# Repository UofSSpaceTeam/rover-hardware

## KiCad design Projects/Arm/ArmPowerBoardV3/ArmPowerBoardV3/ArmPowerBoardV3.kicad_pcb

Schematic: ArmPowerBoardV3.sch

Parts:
BT1: 24vin; TerminalBlock_1x02_P5.08mm_Horizontal
C1, C7, C9, C10, C11: 100nF; C_0805_2012Metric_Pad1.15x1.40mm_HandSolder
C2, C4: 22pF; C_0805_2012Metric_Pad1.15x1.40mm_HandSolder
C3: 220uF; CP_Elec_8x10
C5, C6: 10pF; C_0805_2012Metric_Pad1.15x1.40mm_HandSolder
C8: 10 uF; C_0805_2012Metric_Pad1.15x1.40mm_HandSolder
D1: D_Zener; D_SMB_Handsoldering
D2: LED; LED_D5.0mm_IRGrey
J1: Screw_Terminal_01x04; TerminalBlock_Big4pin
J2, J3, J5, J6, J7: Barrel_Jack; BarrelJack_Wuerth_6941xx301002
J4: Screw_Terminal_01x02; TerminalBlock_1x02_P5.08mm_Horizontal
J8: Gpio out; PinHeader_2x10_P2.54mm_Vertical
J9: Breakout L; PinHeader_1x09_P2.54mm_Vertical
J10: Atmega Holder; DIP-28_W7.62mm
J11: Breakout R; PinHeader_1x09_P2.54mm_Vertical
J13: JST serial; JST_PH_B7B-PH-SM4-TB_1x07-1MP_P2.00mm_Vertical
R2: R; R_Axial_DIN0204_L3.6mm_D1.6mm_P5.08mm_Horizontal
U1: ACS758; Allegro_CB_PSF
U2: VHB200W-Q24-S12; CONV_VHB200W-Q24-S12
U3: V7805-1000
U4: Temp sense; SOT-23_Handsoldering
Y1: Crystal; Crystal_HC49-U_Vertical

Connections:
5v+: C1.2, C6.1, C7.2, C9.2, C10.2, C11.2, J5.1, J6.1, J7.1, J8.1, J8.2, J8.3, J8.4, J9.4, J10.7, J10.20, J10.21, J13.7, U1.1, U3.3 (OUT), U4.1
12v+: J1.2, J1.4, J2.1, J3.1, U2.9
12v-: J1.1, J1.3, J2.2, J3.2, U2.5
24v: C5.1, J4.2, U1.5, U2.1, U3.1 (IN)
GND: BT1.1, C1.1, C2.2, C3.2, C4.2, C5.2, C6.2, C7.1, C8.2, C9.1, C10.1, C11.1, D1.2, J4.1, J5.2, J6.2, J7.2, J8.18, J8.19, J8.20, J9.1, J10.8, J10.22, J13.5, R2.2, U1.2, U2.4, U3.2 (GND), U4.3
ISense: J10.23, U1.3
unnamed: BT1.2, C3.1, C8.1, D1.1, U1.4
unnamed: C2.1, J10.9, Y1.1
unnamed: C4.1, J10.10, Y1.2
unnamed: D2.1, R2.1
unnamed: D2.2, J10.4
unnamed: J8.10, J10.1
unnamed: J8.9, J10.5
unnamed: J8.8, J10.11
unnamed: J8.7, J10.12
unnamed: J8.6, J10.13
unnamed: J8.5, J10.14
unnamed: J8.17, J10.17
unnamed: J8.16, J10.18
unnamed: J8.15, J10.19
unnamed: J8.14, J10.25
unnamed: J8.13, J10.26
unnamed: J8.12, J10.27
unnamed: J8.11, J10.28
ONoff: J10.6, U2.2
RX1: J10.15, J13.2
Rx: J10.2, J11.9
TX1: J10.16, J13.3
TempSense: J10.24, U4.2
Tx: J10.3, J11.5

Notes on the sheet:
Power IN
Temperature Sensor
Headers for USB breakoutboard
JST UART Port
12v Power Supply
Power OUT
5v Power Supply
MCU
change to 0805

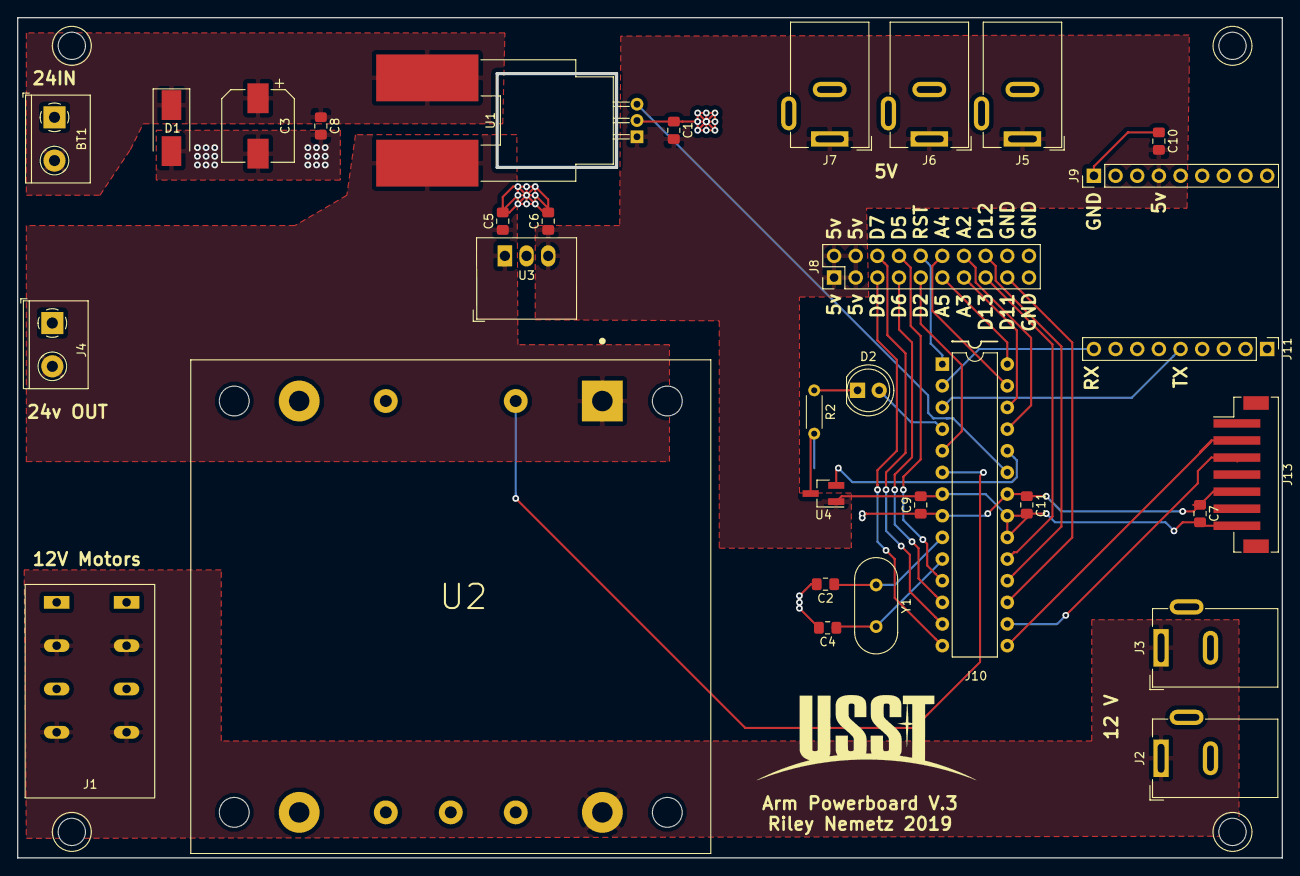
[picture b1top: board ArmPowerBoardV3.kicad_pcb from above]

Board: 2 copper layers, 148.3 x 98.6 mm, 32 parts (0 on the bottom side), 30 nets.

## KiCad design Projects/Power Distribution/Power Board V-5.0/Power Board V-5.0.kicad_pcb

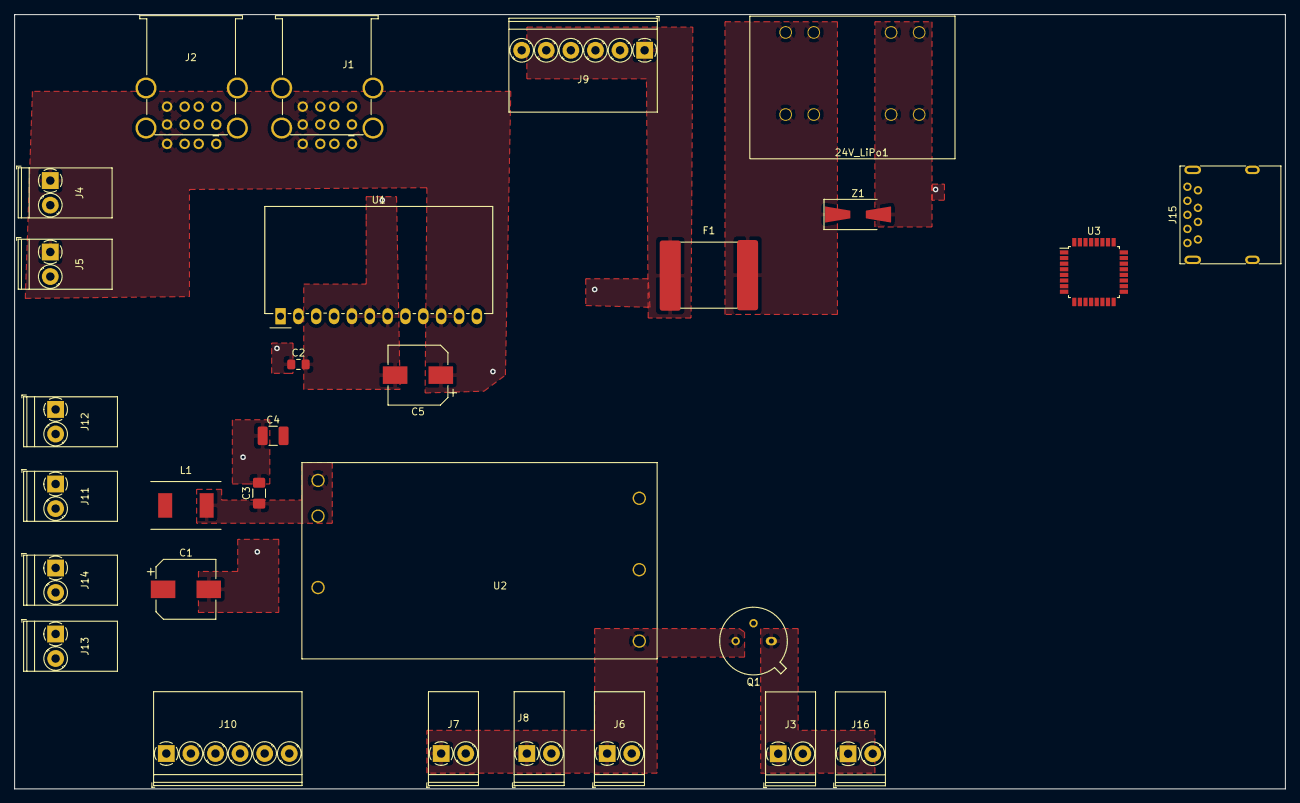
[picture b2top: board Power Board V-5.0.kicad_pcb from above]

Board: 2 copper layers, 180.8 x 110.2 mm, 29 parts (0 on the bottom side), 11 nets, no tracks yet.

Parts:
24V_LiPo1: Battery; Molex_80A
C1, C5: 100uF; CP_Elec_8x10
C2: 1uF; C_0805_2012Metric_Pad1.15x1.40mm_HandSolder
C3: 6.8uF; C_1206_3216Metric_Pad1.42x1.75mm_HandSolder
C4: 6.8nF; C_1210_3225Metric_Pad1.42x2.65mm_HandSolder
F1: 80A; 80A_SMD_Fuse
J1: Pi+Jet; USB_A_PowerONLY_3Stacked
J2: USB xtra; USB_A_PowerONLY_3Stacked
J3, J16: Fans; 2Pos_Tilt_Pheonix
J4, J5: 5v xtra; 2Pos_Tilt_Pheonix
J6: ETH; 2Pos_Tilt_Pheonix
J7, J8: 12v xtra; 2Pos_Tilt_Pheonix
J9: Motors Right terminal; 6Pos_Tilt_Pheonix
J10: Motors left terminal; 6Pos_Tilt_Pheonix
J11: Arm 24v; 2Pos_Tilt_Pheonix
J12: Fr. Atch 24v; 2Pos_Tilt_Pheonix
J13, J14: 24v xtra; 2Pos_Tilt_Pheonix
J15: USB3_A; USB3_A_Molex_48393-001
L1: 4.7uH; Inductor_4.7uH
Q1: 2N2219; TO-39-3
U1: R-745; Converter_DCDC_RECOM_R5xxxDA_THT
U2: RPA60-2412SFW; RPA60
U3: STM8S003K3T; LQFP-32_7x7mm_P0.8mm
Z1: 3w; D_SMA-SMB_Universal_Handsoldering

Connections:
5v+: C5.1, J1.1, J2.1, J4.1, J5.1, U1.9, U1.10, U1.11, U3.7
12v+: J6.1, J7.1, J8.1, Q1.3, U2.6
12v-: C4.2, J3.2, J6.2, J7.2, J8.2, J16.2, U2.5
24v: C1.1, C2.1, F1.1, J9.1, J9.3, J9.5, J10.1, J10.3, J10.5, J11.1, J12.1, J13.1, J14.1, L1.1, U1.2, U1.3, U1.4
GND: 24V_LiPo1.2, C1.2, C2.2, C3.2, C4.1, C5.2, J1.4, J2.4, J4.2, J5.2, J9.2, J9.4, J9.6, J10.2, J10.4, J10.6, J11.2, J12.2, J13.2, J14.2, U1.5, U1.6, U1.7, U1.8, U2.2, U3.4, Z1.2
unnamed: 24V_LiPo1.1, F1.2, Z1.1
unnamed: C3.1, L1.2, U2.1
unnamed: J3.1, J16.1, Q1.1
SCL1_B: J15.8, U3.24
SDA0_B: J15.2, U3.8
SDA1_B: J15.3, U3.23

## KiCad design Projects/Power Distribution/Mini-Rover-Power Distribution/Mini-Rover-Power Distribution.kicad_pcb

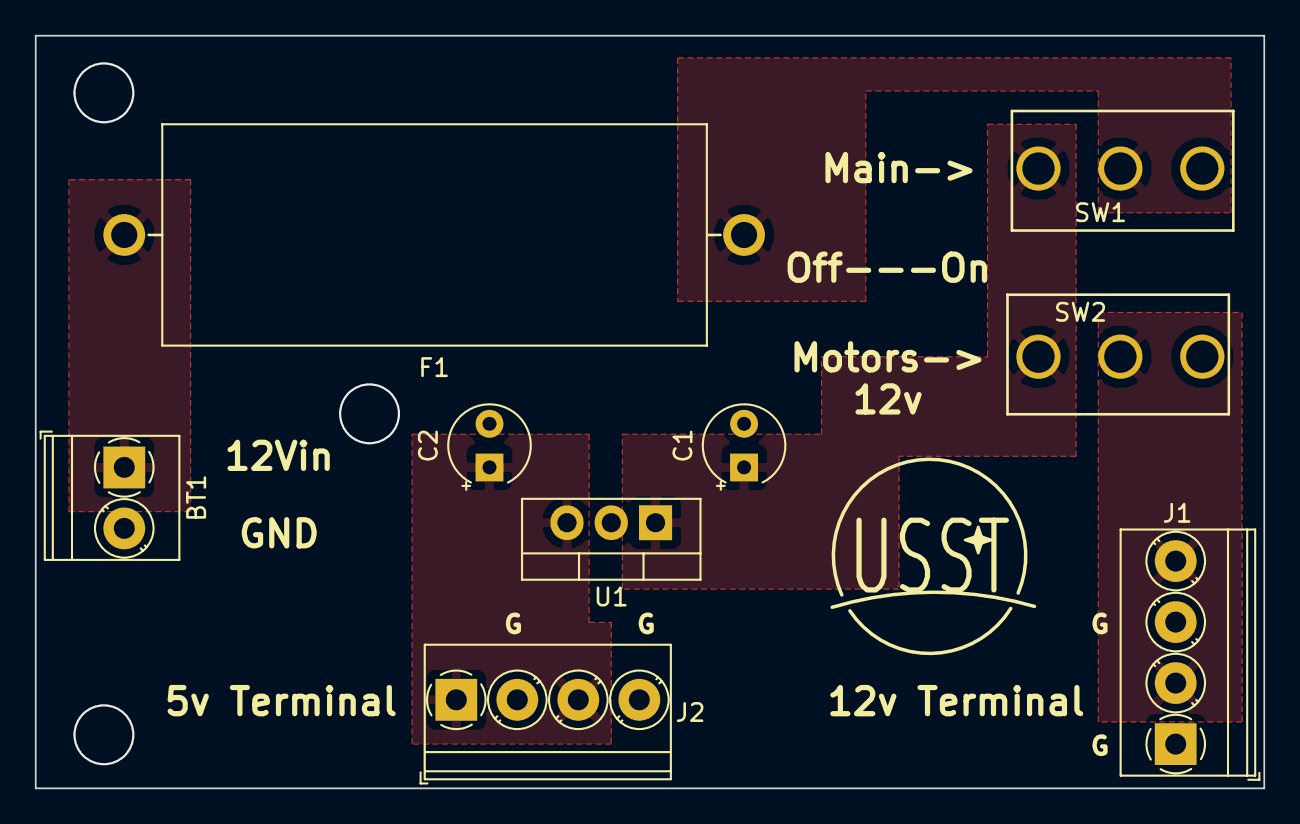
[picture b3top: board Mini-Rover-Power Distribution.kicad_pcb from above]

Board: 2 copper layers, 70.5 x 43.2 mm, 9 parts (0 on the bottom side), 6 nets, no tracks yet.

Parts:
BT1: Battery; TerminalBlock_Phoenix_PT-1,5-2-3.5-H_1x02_P3.50mm_Horizontal
C1: u 0.22F; CP_Radial_Tantal_D4.5mm_P2.50mm
C2: u 0.1F; CP_Radial_Tantal_D4.5mm_P2.50mm
F1: 6.3 A; LittleFuseHolder-03540101ZXGY-
J1, J2: Screw_Terminal_01x04; TerminalBlock_Phoenix_PT-1,5-4-3.5-H_1x04_P3.50mm_Horizontal
SW1, SW2: Toggle Switch; Switch_Toggle
U1: LM7805CT/NOPB; TO-220-3_Vertical

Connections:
/5v: C2.1, J2.1, J2.3, U1.3
/12v: BT1.1, F1.1
GND: BT1.2, C1.2, C2.2, J1.1, J1.3, J2.2, J2.4, U1.2
unnamed: C1.1, SW1.1, SW2.3, U1.1
unnamed: F1.2, SW1.2
unnamed: J1.2, J1.4, SW2.2

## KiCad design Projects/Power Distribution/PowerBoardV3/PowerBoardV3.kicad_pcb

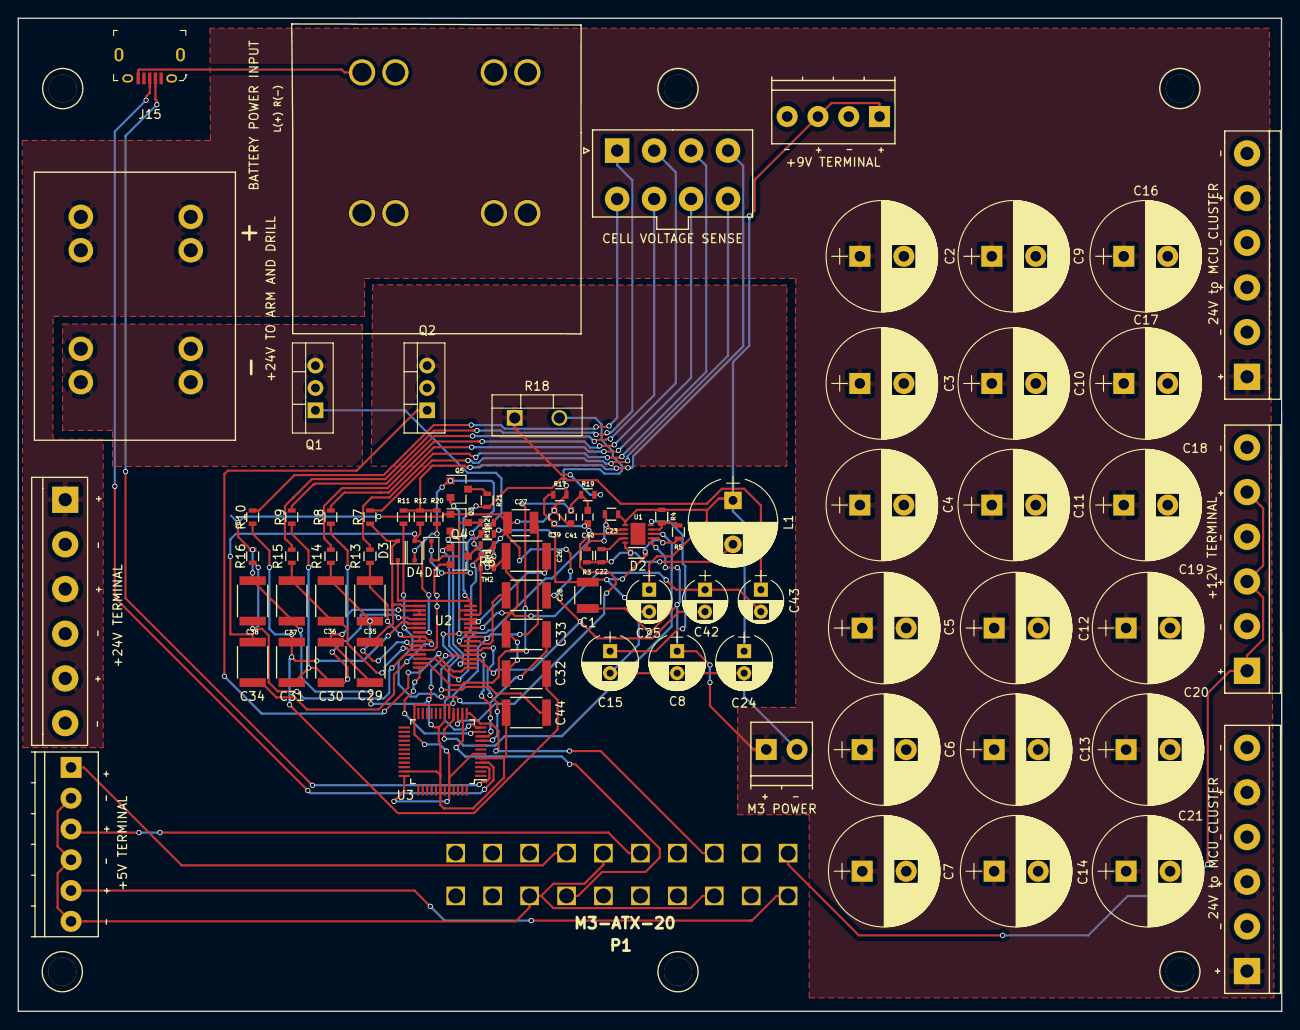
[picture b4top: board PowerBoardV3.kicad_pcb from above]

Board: 2 copper layers, 143.7 x 112.9 mm, 92 parts (0 on the bottom side), 60 nets.

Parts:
24V to MCU CLUSTER: MC_STACK_2; TerminalBlock_Pheonix_PT-5mm_6pol
24V to MCU CLUSTER#2: MC_STACK_1; TerminalBlock_Pheonix_PT-5mm_6pol
+5V TERMINAL: 5V_INT_PWR_BLK; TerminalBlock_Phoenix_PT-3.5mm_6pol
+9V TERMINAL: 9V_PWR_TERMBLK; TerminalBlock_Pheonix_PT-3.5mm_4pol
+12V TERMINAL: 12V_INT_PWR_BLK; TerminalBlock_Pheonix_PT-5mm_6pol
+24V TERMINAL: 24V_INT_PWR_BLK; TerminalBlock_Pheonix_PT-5mm_6pol
+24V TO ARM AND DRILL: BACK_EXT_24V; Phoenix_Contact_1770539
BATTERY POWER INPUT: BATT_PWR; Phoenix_Contact_1845344_Ver2
C1: 4.7uF; C_1210
C2, C3, C4, C5, C6, C7, C9, C10, C11, C12, C13, C14, C16, C17, C18, C19, C20, C21: 680uF; CP_Radial_D12.5mm_P5.00mm
C8, C15: 100uF; CP_Radial_D6.3mm_P2.50mm
C22, C23: 10nF; R_0603
C24: 68uF; CP_Radial_D6.3mm_P2.50mm
C25: 10uF; CP_Radial_D5.0mm_P2.50mm
C26, C28, C29, C30, C31, C32, C33, C34, C35, C36, C37, C38, C44: 1 uF; C_1812
C27: 4.7 uF; C_1210
C39, C40, C41: 0.1uF; C_0603
C42, C43: 10 uF; CP_Radial_D5.0mm_P2.50mm
CELL VOLTAGE SENSE: Cell Voltage Sense; Molex_MiniFit-JR-5556-08A_2x04x4.20mm_Straight
D1: D_Small_ALT; D_SOD-323F
D2: D_Zener_Small_ALT; D_0603
D3, D4: D_Small; D_SOD-323F
J15: USB_OTG; USB_Micro_B_Female_10118194-0001LF
L1: 39uH; CP_Radial_D10.0mm_P5.00mm
M3 POWER: M3-ATX-20-PWR; TerminalBlock_Phoenix_PT-3.5mm_2pol
P1: M3-ATX-20; ATX20
Q1, Q2: IRF3205; TO-220-3_Vertical
Q3: BSS84; SOT-23
Q4: BSS83P; SOT-23
Q5: BSS138; SOT-23
R1, R2: 1M; R_0603
R3: 20k; R_0603
R4: 300k; R_0603
R5: 30k; R_0603
R6: 10k; R_0603
R7, R8, R9, R10, R11, R12, R13, R14, R15, R16: 1k; R_0603
R17, R19, R20, R21: 100; R_0603
R18: 5m; TO-220-2_Vertical_Ver2
TH1, TH2: 10k; R_0603
U1: MP2492; QFN_10
U2: bq76930; 30-TSSOP
U3: SAMD21; TQFP-48_7x7mm_Pitch0.5mm

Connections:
+5V_1: +5V TERMINAL.1, P1.7
+5V_2: +5V TERMINAL.3, P1.11
+5V_3: +5V TERMINAL.5, P1.20
+9V: +9V TERMINAL.1, +9V TERMINAL.3, C23.1, C24.1, C25.1, L1.1, R4.1, U1.6
+12V: +12V TERMINAL.1, +12V TERMINAL.3, +12V TERMINAL.5, P1.19
-5V: +5V TERMINAL.2, +5V TERMINAL.4, +5V TERMINAL.6, P1.6, P1.9, P1.16
-12V: 24V to MCU CLUSTER.2, 24V to MCU CLUSTER.4, 24V to MCU CLUSTER.6, 24V to MCU CLUSTER#2.2, 24V to MCU CLUSTER#2.4, 24V to MCU CLUSTER#2.6, +9V TERMINAL.2, +9V TERMINAL.4, +12V TERMINAL.2, +12V TERMINAL.4, +12V TERMINAL.6, +24V TERMINAL.2, +24V TERMINAL.4, +24V TERMINAL.6, +24V TO ARM AND DRILL.2, C1.2, C2.2, C3.2, C4.2, C5.2, C6.2, C7.2, C8.2, C9.2, C10.2, C11.2, C12.2, C13.2, C14.2, C15.2, C16.2, C17.2, C18.2, C19.2, C20.2, C21.2, C24.2, C25.2, D2.2, M3 POWER.2, P1.10, P1.12, P1.14, Q1.3, R1.2, R5.2, U1.2
/HighPowerCircuit/9V_EN: U1.3, U3.16
/HighPowerCircuit/CHG: Q3.2, U2.2
/HighPowerCircuit/CHG_T: Q1.2, Q2.2
/HighPowerCircuit/DSG: Q2.1, U2.1
/HighPowerCircuit/FB: R4.2, R5.1, U1.4
/HighPowerCircuit/PG: P1.15, U3.13
/HighPowerCircuit/SENSE_R: Q2.3, R18.1, R19.1
/Low Power Circuit /9V_PGOOD: U1.8, U3.15
/Low Power Circuit /PG: P1.8, U3.14
A: CELL VOLTAGE SENSE.4, R11.1, R12.1, R20.2
ALERT: U2.30, U3.11
BAT1: C43.1, D3.1, R21.2, U2.15
BATT+: 24V to MCU CLUSTER.1, 24V to MCU CLUSTER.3, 24V to MCU CLUSTER.5, 24V to MCU CLUSTER#2.1, 24V to MCU CLUSTER#2.3, 24V to MCU CLUSTER#2.5, +24V TERMINAL.1, +24V TERMINAL.3, +24V TERMINAL.5, +24V TO ARM AND DRILL.1, BATTERY POWER INPUT.2, C1.1, C2.1, C3.1, C4.1, C5.1, C6.1, C7.1, C8.1, C9.1, C10.1, C11.1, C12.1, C13.1, C14.1, C16.1, C17.1, C18.1, C19.1, C20.1, C21.1, M3 POWER.1, U1.1
BOOT_MC: Q4.1, U3.12
BOOT_TS1: Q4.3, R6.2
BOOT_VC1: C36.1, C37.2, Q4.2, R15.2, U2.26
CAP2: C26.1, C32.1, C33.2, C42.1, C43.2, D4.1, Q5.1, R20.1, TH2.2, U2.10
CELL_1+: CELL VOLTAGE SENSE.1, R15.1
CELL_2+: CELL VOLTAGE SENSE.2, R14.1
CELL_3+: CELL VOLTAGE SENSE.3, R13.1
CELL_5+: CELL VOLTAGE SENSE.5, R10.1
CELL_6+: CELL VOLTAGE SENSE.6, R9.1
CELL_7+: CELL VOLTAGE SENSE.7, R8.1
CELL_8+: CELL VOLTAGE SENSE.8, R7.1
Cell_1-: BATTERY POWER INPUT.1, C27.2, C28.1, C37.1, C38.2, C39.1, C41.2, C42.2, C44.2, J15.5, Q3.1, R16.1, R17.1, R18.2, TH1.2, U2.3, U3.5, U3.18, U3.35, U3.42
unnamed: C15.1, U1.5
unnamed: C22.1, D2.1, L1.2, R3.2, U1.10
unnamed: C22.2, U1.9
unnamed: C23.2, R3.1, U1.7
unnamed: C26.2, U2.11, U2.12, U2.14
unnamed: C28.2, U2.7
unnamed: C29.1, C30.2, R8.2, U2.17, U2.18
unnamed: C29.2, D3.2, R7.2, U2.16
unnamed: C30.1, C31.2, R9.2, U2.19
unnamed: C31.1, C32.2, R10.2, U2.20
unnamed: C33.1, R11.2, U2.21
unnamed: C34.1, C35.2, R13.2, U2.23, U2.24
unnamed: C34.2, D4.2, R12.2, U2.22
unnamed: C35.1, C36.2, R14.2, U2.25
unnamed: C38.1, R16.2, U2.27
unnamed: D1.1, Q1.1, R1.1, R2.2
unnamed: D1.2, Q3.3, R2.1
unnamed: Q5.3, R21.1
unnamed: R6.1, TH1.1, U2.6
unnamed: TH2.1, U2.13
REGSRC: C44.1, Q5.2, U2.9
SCL: U2.5, U3.9
SDA: U2.4, U3.10
SRN: C40.2, C41.1, R19.2, U2.29
SRP: C39.2, C40.1, R17.2, U2.28
USB_D+: J15.3, U3.4
USB_D-: J15.2, U3.3
VCC: C27.1, U2.8, U3.6, U3.17, U3.36, U3.44

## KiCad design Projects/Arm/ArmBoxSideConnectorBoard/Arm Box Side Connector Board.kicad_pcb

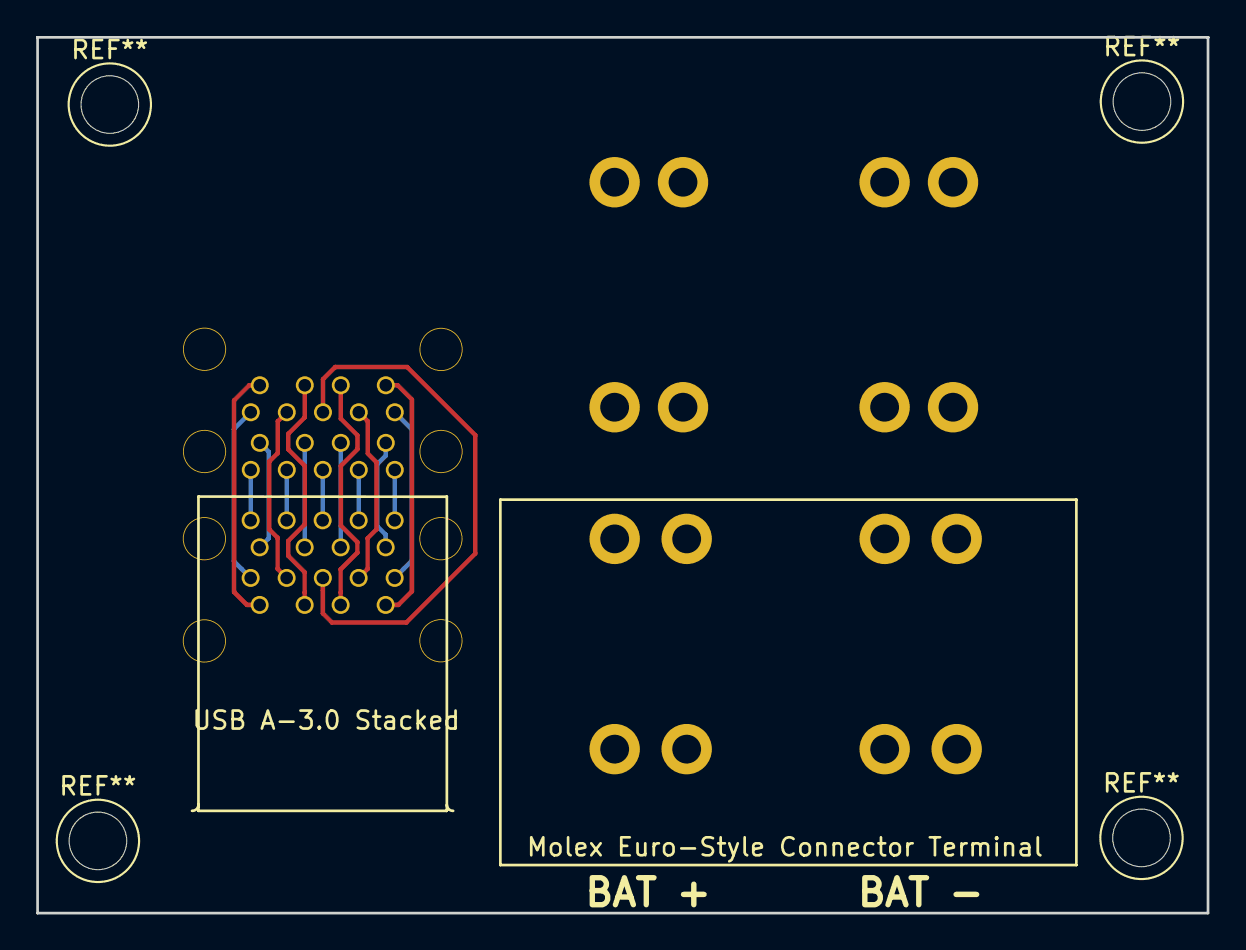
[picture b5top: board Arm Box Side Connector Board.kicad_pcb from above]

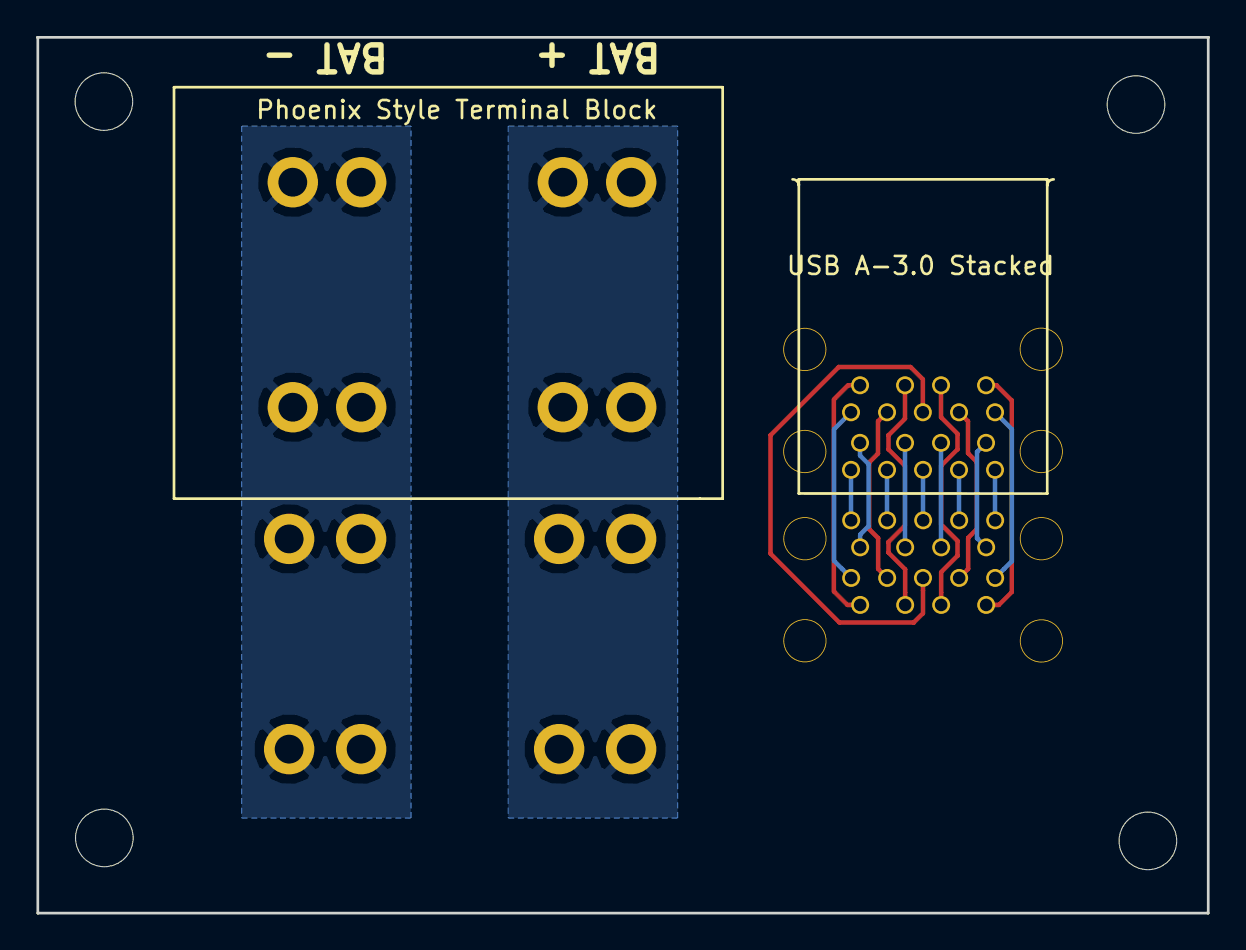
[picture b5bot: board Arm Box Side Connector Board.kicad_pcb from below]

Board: 2 copper layers, 65.1 x 48.7 mm, 4 parts (2 on the bottom side), 20 nets.

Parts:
Molex Euro-Style Connector Terminal: PowerConnector; MolexEuroStyleTerminalBlock2Position
Phoenix Style Terminal Block: PowerConnector; Phoenix_Contact_1770539
USB A-3.0 Stacked, USB A-3.0 Stacked#2: Conn_02x09_Odd_Even; USB-A_3.0_Stacked_WM10420-ND

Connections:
unnamed: USB A-3.0 Stacked.1, USB A-3.0 Stacked#2.1
unnamed: USB A-3.0 Stacked.2, USB A-3.0 Stacked#2.2
unnamed: USB A-3.0 Stacked.3, USB A-3.0 Stacked#2.3
unnamed: USB A-3.0 Stacked.4, USB A-3.0 Stacked#2.4
unnamed: USB A-3.0 Stacked.5, USB A-3.0 Stacked#2.5
unnamed: USB A-3.0 Stacked.6, USB A-3.0 Stacked#2.6
unnamed: USB A-3.0 Stacked.7, USB A-3.0 Stacked#2.7
unnamed: USB A-3.0 Stacked.8, USB A-3.0 Stacked#2.8
unnamed: USB A-3.0 Stacked.9, USB A-3.0 Stacked#2.9
unnamed: USB A-3.0 Stacked.10, USB A-3.0 Stacked#2.10
unnamed: USB A-3.0 Stacked.11, USB A-3.0 Stacked#2.11
unnamed: USB A-3.0 Stacked.12, USB A-3.0 Stacked#2.12
unnamed: USB A-3.0 Stacked.13, USB A-3.0 Stacked#2.13
unnamed: USB A-3.0 Stacked.14, USB A-3.0 Stacked#2.14
unnamed: USB A-3.0 Stacked.15, USB A-3.0 Stacked#2.15
unnamed: USB A-3.0 Stacked.16, USB A-3.0 Stacked#2.16
unnamed: USB A-3.0 Stacked.17, USB A-3.0 Stacked#2.17
unnamed: USB A-3.0 Stacked.18, USB A-3.0 Stacked#2.18
unnamed: Molex Euro-Style Connector Terminal.1, Phoenix Style Terminal Block.1
unnamed: Molex Euro-Style Connector Terminal.2, Phoenix Style Terminal Block.2

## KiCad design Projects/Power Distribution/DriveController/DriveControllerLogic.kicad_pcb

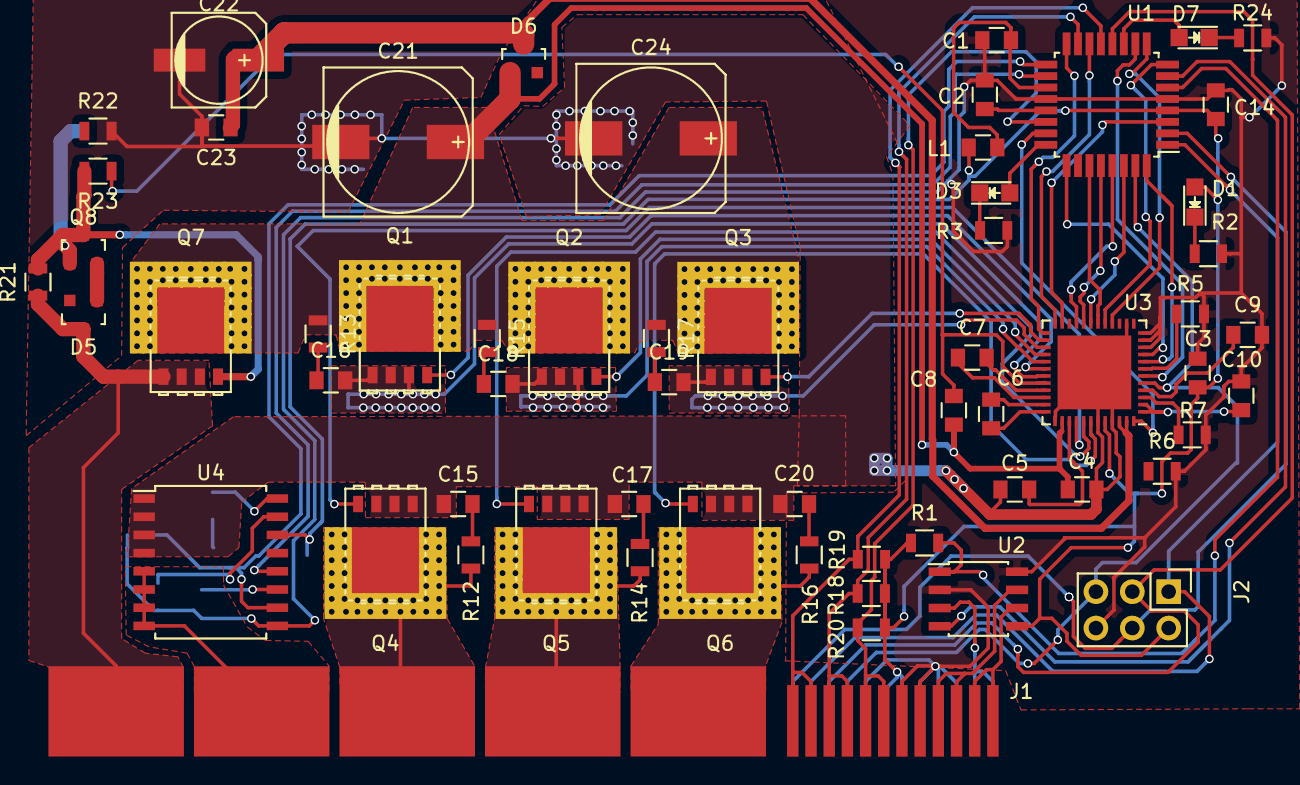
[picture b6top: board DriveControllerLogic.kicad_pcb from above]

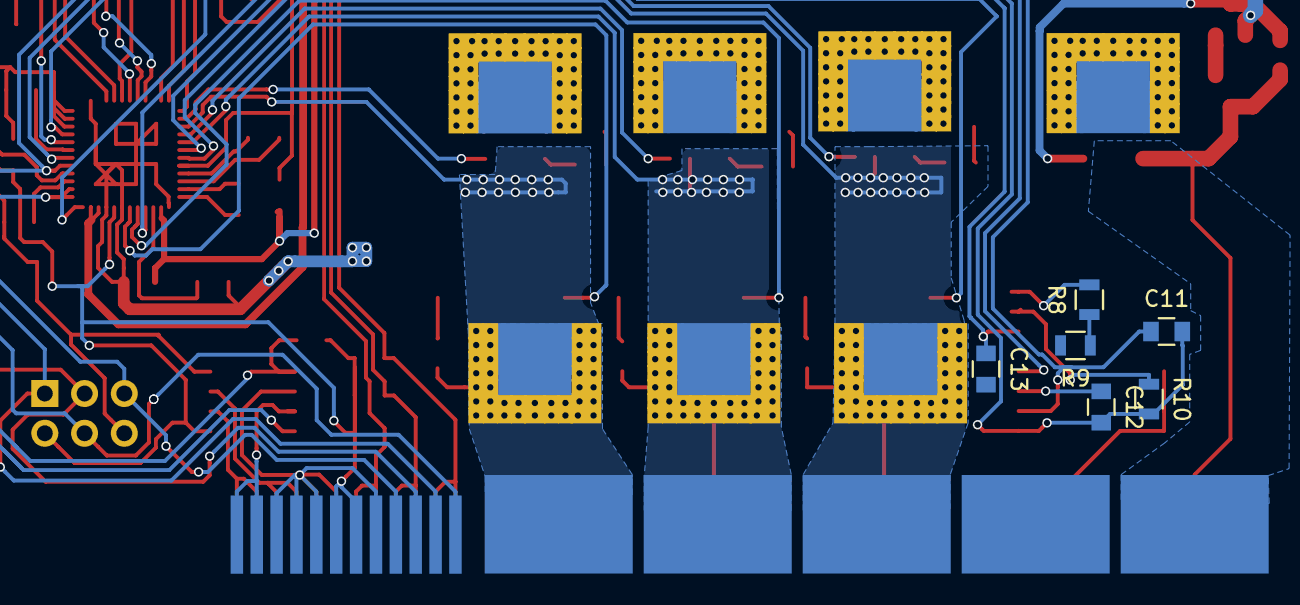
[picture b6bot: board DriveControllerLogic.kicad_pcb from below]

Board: 2 copper layers, 66 parts (6 on the bottom side), 73 nets.

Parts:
C1, C4, C6, C7, C13, C23: 100nF; C_0805
C2, C14, C15, C16, C17, C18, C19, C20: 10nF; C_0805
C3: 2.2uF; C_0805
C5, C8: 470nF; C_0805
C9: 220pF; C_0805
C10: 220nF; C_0805
C11, C12: 1nF; C_0805
C21, C24: 220uF; c_elec_10x10
C22: 22uF; c_elec_6.3x5.7
D1: LED_PWR; LED-0805
D3: LED_STAT; LED-0805
D5, D6: BAS16; SOT-23
D7: LED_CAN; LED-0805
J1: HPCE_40-24; HPCE-40-24
J2: ISP_Header; Pin_Header_Straight_2x03
L1: 10uH; C_0805
Q1, Q2, Q3, Q4, Q5, Q6, Q7: PSMN1R0; SOT-669_LFPAK_POWERSO8
Q8: BC817-40; SOT-23
R1, R6, R18, R19, R20, R22, R23: 10k; R_0805
R2, R3, R24: 1k; R_0805
R5: 0 (J); R_0805
R7: 33k; R_0805
R8, R9, R21: 100k; R_0805
R10: 47k; R_0805
R12, R13, R14, R15, R16, R17: 10; R_0805
U1: ATMega32M1; TQFP-32_7x7mm_Pitch0.8mm
U2: MCP2562; SOIC-8_3.9x4.9mm_Pitch1.27mm
U3: ATA6844; QFN-48-1EP_7x7mm_Pitch0.5mm
U4: ACS710; SOIC-16_7.5x10.3mm_Pitch1.27mm

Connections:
/5V0: C3.1, C13.1, C14.1, D1.2, J1.58, J1.59, J2.2, L1.1, R1.1, R18.1, R19.1, R20.1, U1.4, U2.5, U3.44, U4.14
/CANH: J1.49, J1.50, U2.7
/CANL: J1.51, J1.52, U2.6
/DG1: U1.3, U3.23
/DG2: U1.14, U3.24
/DG3: U1.16, U3.25
/DriveControllerPower/CPOUT: C8.2, R23.1, U3.32
/DriveControllerPower/H1: Q1.1, U3.30
/DriveControllerPower/H2: Q2.1, U3.28
/DriveControllerPower/H3: Q3.1, U3.26
/DriveControllerPower/L1: Q4.1, U3.40
/DriveControllerPower/L2: Q5.1, U3.41
/DriveControllerPower/L3: Q6.1, U3.42
/DriveControllerPower/PBAT: C4.2, C8.1, C21.1, C24.1, D6.1, Q1.5, Q2.5, Q3.5, Q7.5, R13.1, R15.1, R17.1, U3.38
/DriveControllerPower/POUT: C4.1, C5.1, C15.2, C17.2, C20.2, C21.2, C22.2, C23.2, C24.2, Q4.3, Q5.3, Q6.3, R22.2, U3.14, U3.37, U3.43, U3.45, U3.49, U4.1, U4.2, U4.3, U4.4
/DriveControllerPower/U: C16.2, J1.9, J1.29, Q1.3, Q4.5, R12.1, U3.31
/DriveControllerPower/V: C18.2, J1.13, J1.25, Q2.3, Q5.5, R14.1, U3.29
/DriveControllerPower/VBAT: C22.1, C23.1, D6.3, U3.46, U3.47
/DriveControllerPower/VSUPPLY: D5.3, J1.1, J1.37, Q7.3, R21.1
/DriveControllerPower/W: C19.2, J1.17, J1.21, Q3.3, Q6.5, R16.1, U3.27
/HA1: J1.41, J1.42, R19.2, U1.13
/HA2: J1.43, J1.44, R18.2, U1.15
/HA3: J1.45, J1.46, R20.2, U1.22
/IFL_EN: R8.2, U4.16
/IH1: U1.29, U3.21
/IH2: U1.30, U3.19
/IH3: U1.8, U3.17
/IL1: U1.28, U3.20
/IL2: U1.27, U3.18
/IL3: U1.9, U3.16
/ISENSEN: C11.1, U1.17, U4.10
/ISENSEP: U1.18, U4.12
/LGND: C1.2, C2.2, C3.2, C9.2, C10.2, C11.2, C12.2, C13.2, C14.2, J1.47, J1.48, J1.55, J1.56, J1.57, J1.60, J2.6, R2.2, R3.2, R5.2, R6.2, R7.2, R10.2, R24.2, U1.5, U1.20, U2.2, U2.8, U3.10, U3.11, U3.12, U4.9
/MISO: J1.63, J2.1, U1.1
/MOSI: J1.64, J2.4, U1.2
/NCOAST: U1.23, U3.48
/NRESET: J1.61, J2.5, U1.31, U3.5
/PGND: J1.5, J1.33, U4.5, U4.6, U4.7, U4.8
/RXCAN: U1.7, U2.4
/SCK: J1.62, J2.3, U1.12
/SCREF: U1.25, U3.9
/SLEEP: U1.32, U3.8
/STATCAN: D7.2, U1.11
/STAT_LED: D3.2, U1.24
/TXCAN: R1.2, U1.6, U2.1
/VCAN: J1.53, J1.54, U2.3
/WD: U1.10, U3.6
unnamed: C1.1, L1.2, U1.19
unnamed: C2.1, U1.21
unnamed: C5.2, U3.39
unnamed: C6.1, U3.36
unnamed: C6.2, U3.35
unnamed: C7.1, U3.34
unnamed: C7.2, U3.33
unnamed: C9.1, R6.1, U3.4
unnamed: C10.1, U3.1, U3.2
unnamed: C12.1, U4.11
unnamed: C15.1, R12.2
unnamed: C16.1, R13.2
unnamed: C17.1, R14.2
unnamed: C18.1, R15.2
unnamed: C19.1, R17.2
unnamed: C20.1, R16.2
unnamed: D1.1, R2.1
unnamed: D3.1, R3.1
unnamed: D5.1, Q8.2
unnamed: D7.1, R24.1
unnamed: Q7.1, Q8.3, R21.2, R23.2
unnamed: Q8.1, R22.1
unnamed: R5.1, U3.7
unnamed: R7.1, U3.3
unnamed: R8.1, R9.1
unnamed: R9.2, R10.1, U4.15

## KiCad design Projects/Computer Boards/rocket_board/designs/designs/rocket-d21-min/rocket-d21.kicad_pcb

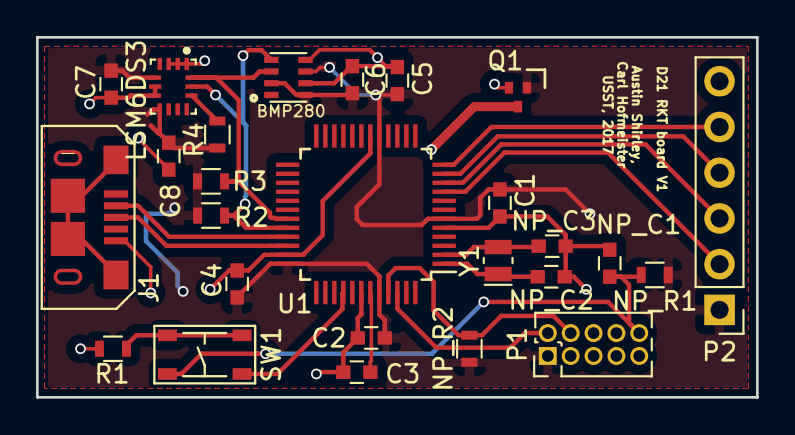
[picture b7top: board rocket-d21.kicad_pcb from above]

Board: 2 copper layers, 40.0 x 20.0 mm, 27 parts (1 on the bottom side), 21 nets.

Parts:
BT1: BK-883; BK-833
C1, C2, C4, C5, C6, C7, C8: 100n; C_0603
C3: 1u; C_0603
J1: USB_MICRO_RIGHT; MF_Connectors-MICROUSB-RIGHT
NP_C1: 100n; C_0603
NP_C2, NP_C3: 15p; C_0603
NP_R1: 10k; R_0603
NP_R2: 1k; R_0603
P1: SWD_CONN; Pin_Header_Straight_2x05_Pitch1.27mm
P2: CONN_01X06; Pin_Header_Straight_1x06_Pitch2.54mm
Q1: RE1C002UN; SOT-490
R1: 330; R_0603
R2, R3: 4.7k; R_0603
R4: 10k; R_0603
SW1: TACT_4.2MM; MF_Switches-TACT4.2MM
U1: ATSAMD21G18A; TQFP-48_7x7mm_Pitch0.5mm
U2: LSM6DS3; LGA-14
U3: BMP280; LGA-8
Y1: ABS06-107-32.768KHZ-T; Crystal_SMD_MicroCrystal_CC8V-T1A-2pin_2.0x1.2mm

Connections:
+3.3VP: BT1.1, C1.2, C2.2, C4.2, C5.1, C6.1, C7.1, C8.2, NP_R1.1, NP_R2.1, P1.1, P2.1, Q1.1, R2.1, R3.1, R4.1, U1.6, U1.17, U1.36, U1.44, U2.5, U2.8, U3.2, U3.6, U3.8
/A4: P2.2, U1.9
/A5: P2.3, U1.10
/GPIO2: P2.4, U1.11
/GPIO3: P2.5, U1.12
/SCL: R2.2, U1.32, U2.13, U3.4
/SDA: R3.2, U1.31, U2.14, U3.3
/SWCLK: NP_R2.2, P1.4, U1.45
/SWDIO: P1.2, U1.46
/USB_D+: J1.3, U1.34
/USB_D-: J1.2, U1.33
/~RESET: NP_C1.2, NP_R1.2, P1.10, SW1.3
GND: C1.1, C2.1, C3.2, C4.1, C5.2, C6.2, C7.2, C8.1, J1.5, NP_C1.1, NP_C2.1, NP_C3.1, P1.3, P1.5, P2.6, Q1.2, R1.1, U1.5, U1.18, U1.35, U1.42, U2.1, U2.2, U2.3, U2.6, U2.7, U3.5, U3.7
unnamed: BT1.2, Q1.3
unnamed: C3.1, U1.43
unnamed: NP_C2.2, U1.1, Y1.1
unnamed: NP_C3.2, U1.2, Y1.2
unnamed: R1.2, SW1.1, SW1.2
unnamed: R4.2, U2.12
unnamed: SW1.4, U1.40
SLD: J1.S1, J1.S2, J1.S3, J1.S4, J1.S5, J1.S6

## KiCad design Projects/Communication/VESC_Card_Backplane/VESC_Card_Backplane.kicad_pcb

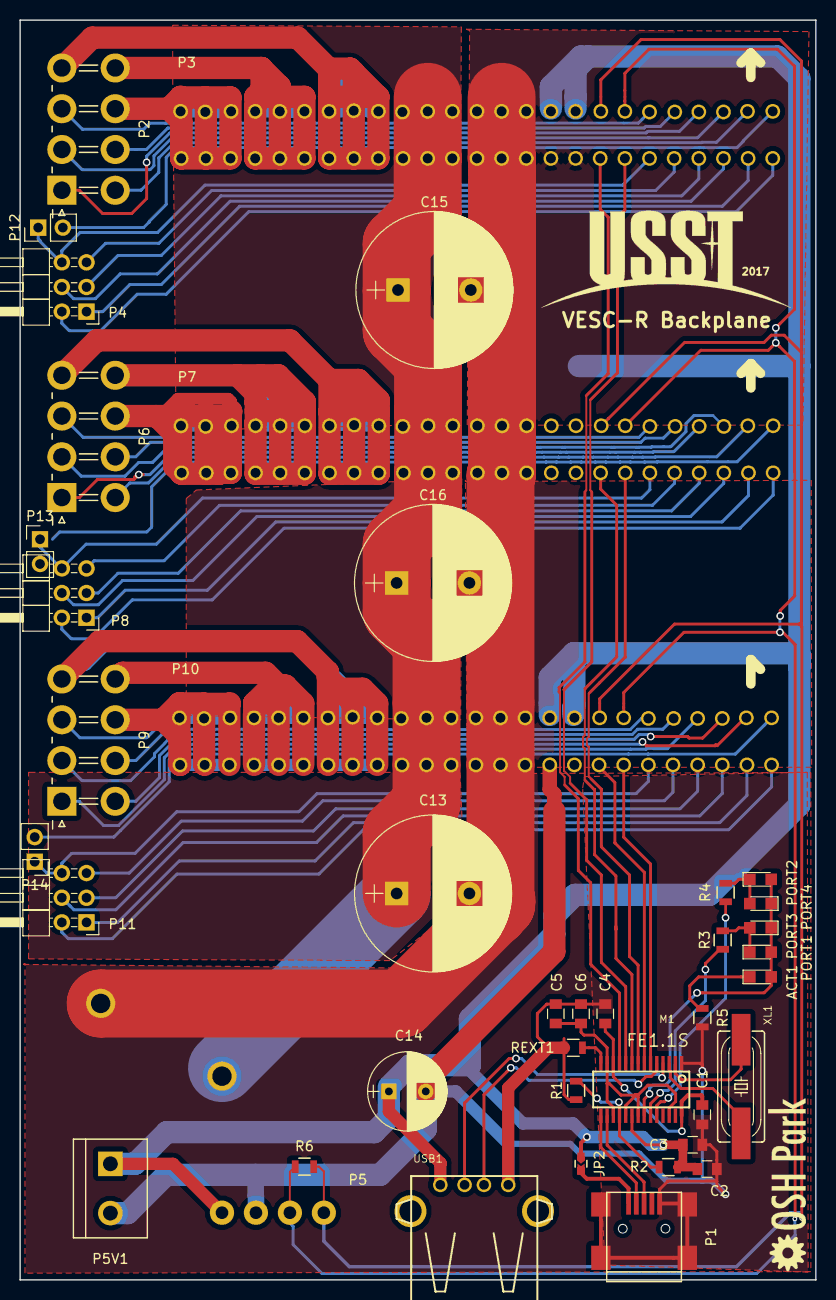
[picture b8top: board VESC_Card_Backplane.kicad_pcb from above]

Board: 2 copper layers, 82.0 x 129.8 mm, 42 parts (1 on the bottom side), 74 nets.

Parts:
ACT1: LED_0805
C1, C2, C5: 10uF; C_0805
C3, C4, C6: 0.1uF; C_0805
C13, C15, C16: 2200u; CP_Radial_D16.0mm_P7.50mm
C14: 100u; CP_Radial_D8.0mm_P3.80mm
JP2: J; J_0603
M1: FE1.1S; FE1.1S_SSOP-28
P1: USB_OTG; USB_Mini-B
P2, P6, P9: EC90_Flat; Molex_MiniFit-JR-5569-08A2_2x04x4.20mm_Angled_Overhang
P3, P7, P10: AMP17614426-2_EDGE; TE2007088-1_Backplane2
P4, P8, P11: CONN_01X06; Pin_Header_Angled_2x03_Pitch2.54mm
P5: CONN_01X04; Molex_39502_1004R
P5V1: CONN_01X02; Molex_39531_1002
P12, P13, P14: CONN_01X02; Pin_Header_Straight_1x02_Pitch2.54mm
PBAT1: CONN_01X02; Phoenix_Contact_PLA5
PORT1, PORT2, PORT3, PORT4: LED_0805
R1: 100K; R_0805
R2: 47K; R_0805
R3, R4, R5: 330; R_0805
R6: 120; R_0805
REXT1: 2.7K; R_0805
USB1: USB-TYPA; USB_A_PTH_AMP787616-1
XL1: 12MHz; HC49UP_SMT_Crystal

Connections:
+5V: C2.1, C3.1, C14.1, JP2.1, M1.20, P3.6, P3.7, P5.1, P5V1.1, P7.6, P7.7, P10.6, P10.7, R2.1, USB1.VBUS
/CANH: P3.8, P5.4, P7.8, P10.8, R6.2
/CAN_Bus/CANL: P3.9, P5.3, P7.9, P10.9, R6.1
/DM_4: M1.4, USB1.D-
/DP_4: M1.5, USB1.D+
/Motor_Controller_A/GND_AUX: P3.21, P4.6, P12.1
/Motor_Controller_A/H1: P2.1, P3.12
/Motor_Controller_A/H2: P2.2, P3.13
/Motor_Controller_A/H3: P2.5, P3.14
/Motor_Controller_A/W: P2.7, P3.1, P3.30
/Motor_Controller_A/X: P2.8, P3.2, P3.29
/Motor_Controller_A/Y: P2.4, P3.3, P3.28
/Motor_Controller_B/GND_AUX: P7.21, P8.6, P13.1
/Motor_Controller_B/H1: P6.1, P7.12
/Motor_Controller_B/H2: P6.2, P7.13
/Motor_Controller_B/H3: P6.5, P7.14
/Motor_Controller_B/W: P6.7, P7.1, P7.30
/Motor_Controller_B/X: P6.8, P7.2, P7.29
/Motor_Controller_B/Y: P6.4, P7.3, P7.28
/Motor_Controller_C/GND_AUX: P10.21, P11.6, P14.1
/Motor_Controller_C/H1: P9.1, P10.12
/Motor_Controller_C/H2: P9.2, P10.13
/Motor_Controller_C/H3: P9.5, P10.14
/Motor_Controller_C/W: P9.7, P10.1, P10.30
/Motor_Controller_C/X: P9.8, P10.2, P10.29
/Motor_Controller_C/Y: P9.4, P10.3, P10.28
/PGND: C13.2, C15.2, C16.2, P3.5, P3.24, P3.25, P3.26, P7.5, P7.24, P7.25, P7.26, P10.5, P10.26, PBAT1.2
/USB_DM_1: M1.10, P3.22
/USB_DM_2: M1.8, P7.22
/USB_DM_3: M1.6, P10.22
/USB_DP_1: M1.11, P3.23
/USB_DP_2: M1.9, P7.23
/USB_DP_3: M1.7, P10.23
/USB_Hub/DM_U: M1.15, P1.2
/USB_Hub/DP_U: M1.16, P1.3
/USB_Hub/N$1: M1.14, REXT1.2
/USB_Hub/N$6: PORT2.1, PORT4.2, R4.2
/USB_Hub/N$7: M1.2, XL1.2
/USB_Hub/N$8: C1.1, C4.1, M1.12, M1.28
/USB_Hub/N$9: M1.3, XL1.1
/USB_Hub/N$13: M1.18, R1.1, R2.2
/USB_Hub/N$20: PORT1.1, PORT3.2, R3.2
/USB_Hub/N$22: ACT1.1, R5.1
/USB_Hub/N$23: M1.23, R3.1
/USB_Hub/N$24: M1.24, R4.1
/USB_Hub/N$25: ACT1.2, M1.22, PORT1.2, PORT2.2, PORT3.1, PORT4.1
/VBAT: C13.1, C15.1, C16.1, P3.4, P3.27, P7.4, P7.27, P10.4, P10.27, PBAT1.1
GND: C1.2, C2.2, C3.2, C4.2, C5.2, C6.2, C14.2, M1.1, P1.5, P1.6, P5.2, P5V1.2, P10.24, P10.25, R1.2, R5.2, REXT1.1, USB1.GND
unnamed: JP2.2, P1.1
unnamed: P2.3, P3.10
unnamed: P2.6, P3.11
unnamed: P3.16, P4.2
unnamed: P3.17, P4.1
unnamed: P3.18, P4.4
unnamed: P3.19, P4.3
unnamed: P3.20, P4.5
unnamed: P6.3, P7.10
unnamed: P6.6, P7.11
unnamed: P7.16, P8.2
unnamed: P7.17, P8.1
unnamed: P7.18, P8.4
unnamed: P7.19, P8.3
unnamed: P7.20, P8.5
unnamed: P9.3, P10.10
unnamed: P9.6, P10.11
unnamed: P10.15, P14.2
unnamed: P10.16, P11.2
unnamed: P10.17, P11.1
unnamed: P10.18, P11.4
unnamed: P10.19, P11.3
unnamed: P10.20, P11.5
unnamed: P3.15, P12.2
unnamed: P7.15, P13.2
VDD: C5.1, C6.1, M1.13, M1.17, M1.19, M1.21, M1.26
